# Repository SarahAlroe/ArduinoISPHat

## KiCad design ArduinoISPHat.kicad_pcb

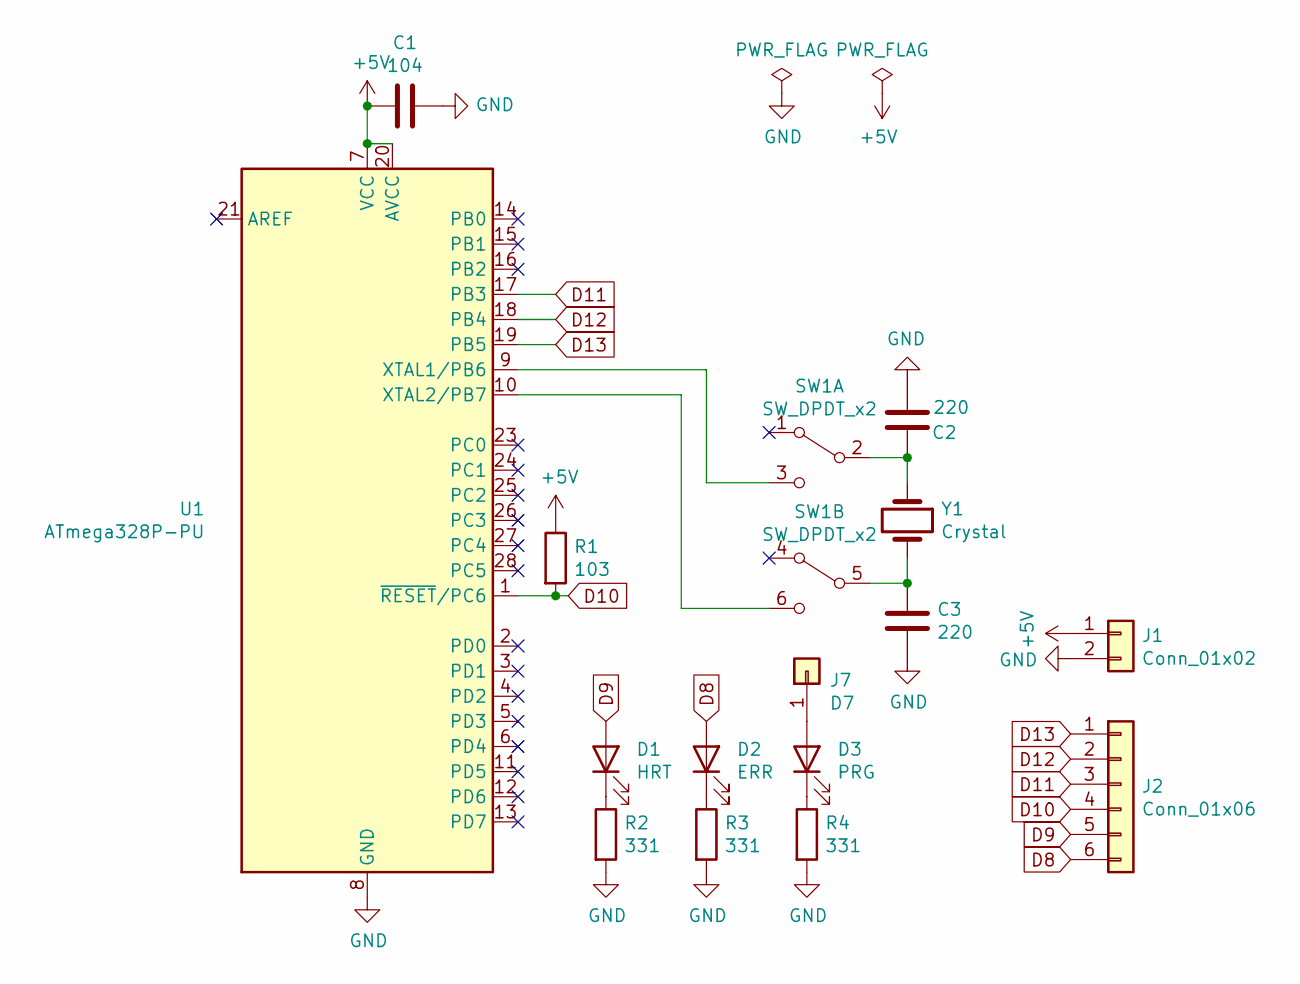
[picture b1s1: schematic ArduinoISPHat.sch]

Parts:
C1: 104; C_Disc_D4.7mm_W2.5mm_P5.00mm
C2, C3: 220; C_Disc_D4.7mm_W2.5mm_P5.00mm
D1: HRT; LED_D5.0mm
D2: ERR; LED_D5.0mm
D3: PRG; LED_D5.0mm
J1: Conn_01x02; PinSocket_1x02_P2.54mm_Vertical
J2: Conn_01x06; PinSocket_1x06_P2.54mm_Vertical
J7: D7; PinSocket_1x01_P2.54mm_Vertical
R1: 103; R_Axial_DIN0207_L6.3mm_D2.5mm_P10.16mm_Horizontal
R2, R3, R4: 331; R_Axial_DIN0207_L6.3mm_D2.5mm_P10.16mm_Horizontal
SW1: SW_DPDT_x2; SW_KFC6X6-A
U1: ATmega328P-PU; DIP-28_W7.62mm
Y1: Crystal; Crystal_HC49-U_Vertical

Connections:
+5V: C1.2, J1.1, R1.1, U1.7 (VCC), U1.20 (AVCC)
D8: D2.2 (A), J2.6
D9: D1.2 (A), J2.5
D10: J2.4, R1.2, U1.1 (~RESET~/PC6)
D11: J2.3, U1.17 (PB3)
D12: J2.2, U1.18 (PB4)
D13: J2.1, U1.19 (PB5)
GND: C1.1, C2.2, C3.2, J1.2, R2.2, R3.2, R4.2, U1.8 (GND), U1.22 (GND)
unnamed: C2.1, SW1.2 (B), Y1.1
unnamed: C3.1, SW1.5 (B), Y1.2
unnamed: D1.1 (K), R2.1
unnamed: D2.1 (K), R3.1
unnamed: D3.1 (K), R4.1
unnamed: D3.2 (A), J7.1
unnamed: SW1.3 (C), U1.9 (XTAL1/PB6)
unnamed: SW1.6 (C), U1.10 (XTAL2/PB7)

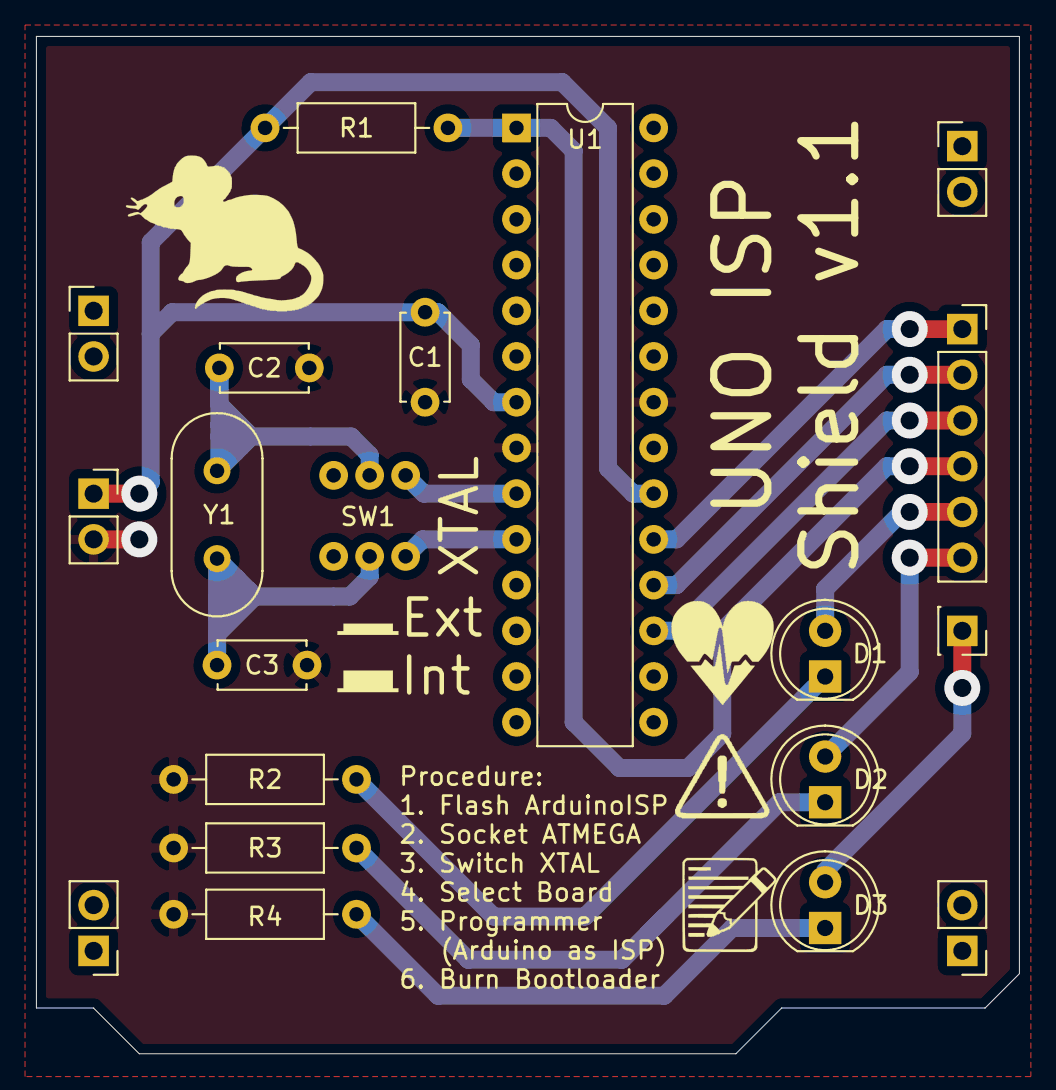
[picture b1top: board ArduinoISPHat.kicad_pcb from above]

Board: 2 copper layers, 54.6 x 56.5 mm, 16 parts (0 on the bottom side), 16 nets.

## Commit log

2020-11-26 Init
2021-08-10 Updated layout
